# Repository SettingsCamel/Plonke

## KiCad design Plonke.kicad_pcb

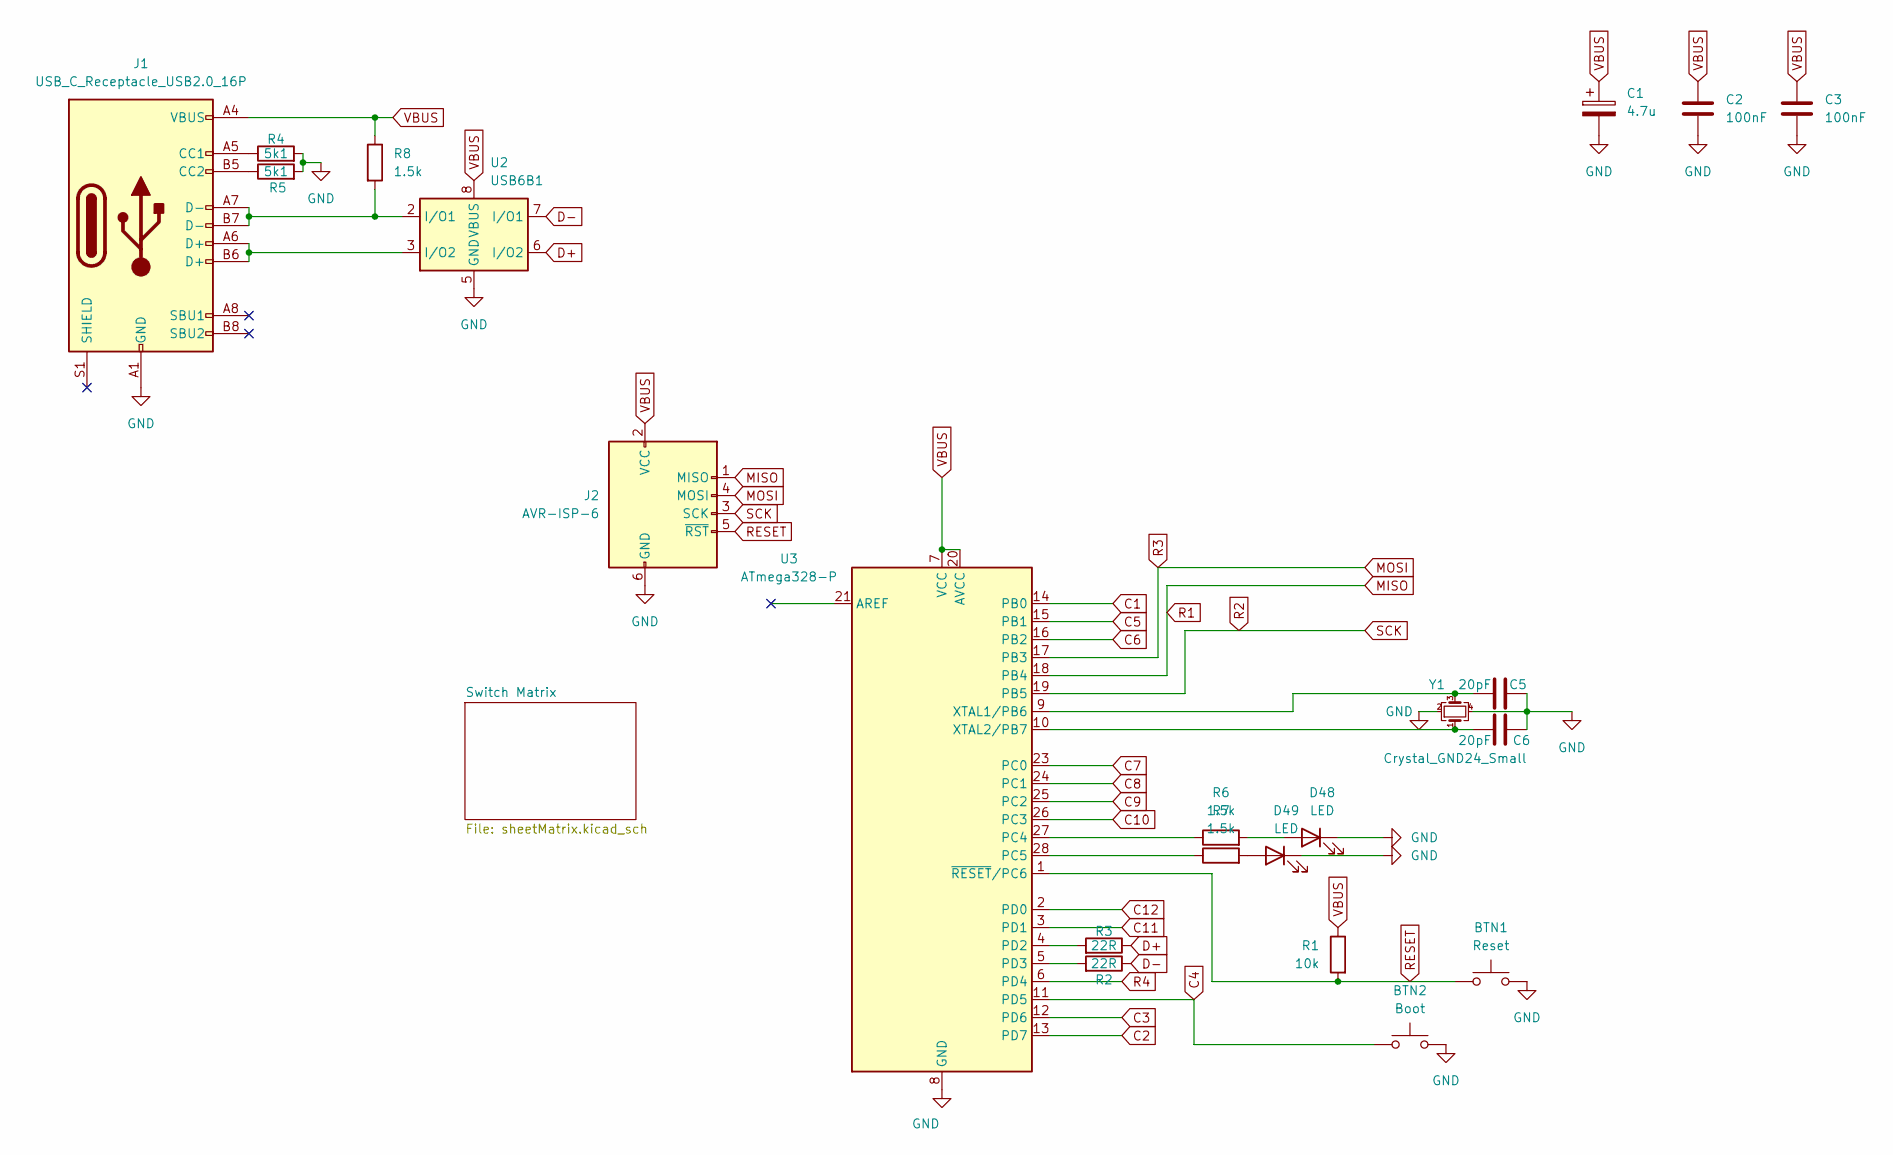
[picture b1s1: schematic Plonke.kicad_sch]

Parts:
BTN1: Reset; SW_PUSH_6mm
BTN2: Boot; SW_PUSH_6mm
C1: 4.7u; CP_Radial_D4.0mm_P1.50mm
C2, C3: 100nF; C_Disc_D4.7mm_W2.5mm_P5.00mm
C5, C6: 20pF; C_Disc_D4.7mm_W2.5mm_P5.00mm
D48, D49: LED; LED_D3.0mm
J1: USB_C_Receptacle_USB2.0_16P; USB_C_Receptacle_XKB_U262-16XN-4BVC11
J2: AVR-ISP-6; PinHeader_2x03_P2.54mm_Vertical
R1: 10k; R_Axial_DIN0207_L6.3mm_D2.5mm_P10.16mm_Horizontal
R2, R3: 22R; R_Axial_DIN0207_L6.3mm_D2.5mm_P10.16mm_Horizontal
R4, R5: 5k1; R_Axial_DIN0207_L6.3mm_D2.5mm_P10.16mm_Horizontal
R6, R7, R8: 1.5k; R_Axial_DIN0207_L6.3mm_D2.5mm_P10.16mm_Horizontal
U2: USB6B1; SOIC-8_3.9x4.9mm_P1.27mm
U3: ATmega328-P; DIP-28_W7.62mm
Y1: Crystal_GND24_Small; Crystal_HC18-U_Vertical

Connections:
C1: U3.14 (PB0); also elsewhere on the board
C2: U3.13 (PD7); also elsewhere on the board
C3: U3.12 (PD6); also elsewhere on the board
C4: BTN2.2, U3.11 (PD5); also elsewhere on the board
C5: U3.15 (PB1); also elsewhere on the board
C6: U3.16 (PB2); also elsewhere on the board
C7: U3.23 (PC0); also elsewhere on the board
C8: U3.24 (PC1); also elsewhere on the board
C9: U3.25 (PC2); also elsewhere on the board
C10: U3.26 (PC3); also elsewhere on the board
C11: U3.3 (PD1); also elsewhere on the board
C12: U3.2 (PD0); also elsewhere on the board
D+: R3.1, U2.6 (I/O2)
D-: R2.1, U2.7 (I/O1)
GND: BTN1.1, BTN2.1, C1.2, C2.2, C3.2, C5.1, C6.1, D48.1 (K), D49.1 (K), J1.A1 (GND), J1.A12 (GND), J1.B1 (GND), J1.B12 (GND), J2.6 (GND), R4.2, R5.2, U2.4 (GND), U2.5 (GND), U3.8 (GND), U3.22 (GND), Y1.2, Y1.4
MISO: J2.1 (MISO), U3.18 (PB4); also elsewhere on the board
MOSI: J2.4 (MOSI), U3.17 (PB3); also elsewhere on the board
unnamed: D48.2 (A), R6.2
unnamed: D49.2 (A), R7.2
unnamed: J1.A5 (CC1), R4.1
unnamed: J1.B5 (CC2), R5.1
unnamed: J1.A6 (D+), J1.B6 (D+), U2.3 (I/O2)
unnamed: J1.A7 (D-), J1.B7 (D-), R8.2, U2.2 (I/O1)
unnamed: R6.1, U3.27 (PC4)
unnamed: R7.1, U3.28 (PC5)
unnamed: R3.2, U3.4 (PD2)
unnamed: R2.2, U3.5 (PD3)
unnamed: C5.2, U3.9 (XTAL1/PB6), Y1.3
unnamed: C6.2, U3.10 (XTAL2/PB7), Y1.1
R2: J2.3 (SCK), U3.19 (PB5); also elsewhere on the board
R4: U3.6 (PD4); also elsewhere on the board
RESET: BTN1.2, J2.5 (~RST), R1.2, U3.1 (~RESET/PC6)
VBUS: C1.1, C2.1, C3.1, J1.A4 (VBUS), J1.A9 (VBUS), J1.B4 (VBUS), J1.B9 (VBUS), J2.2 (VCC), R1.1, R8.1, U2.1 (VBUS), U2.8 (VBUS), U3.7 (VCC), U3.20 (AVCC)

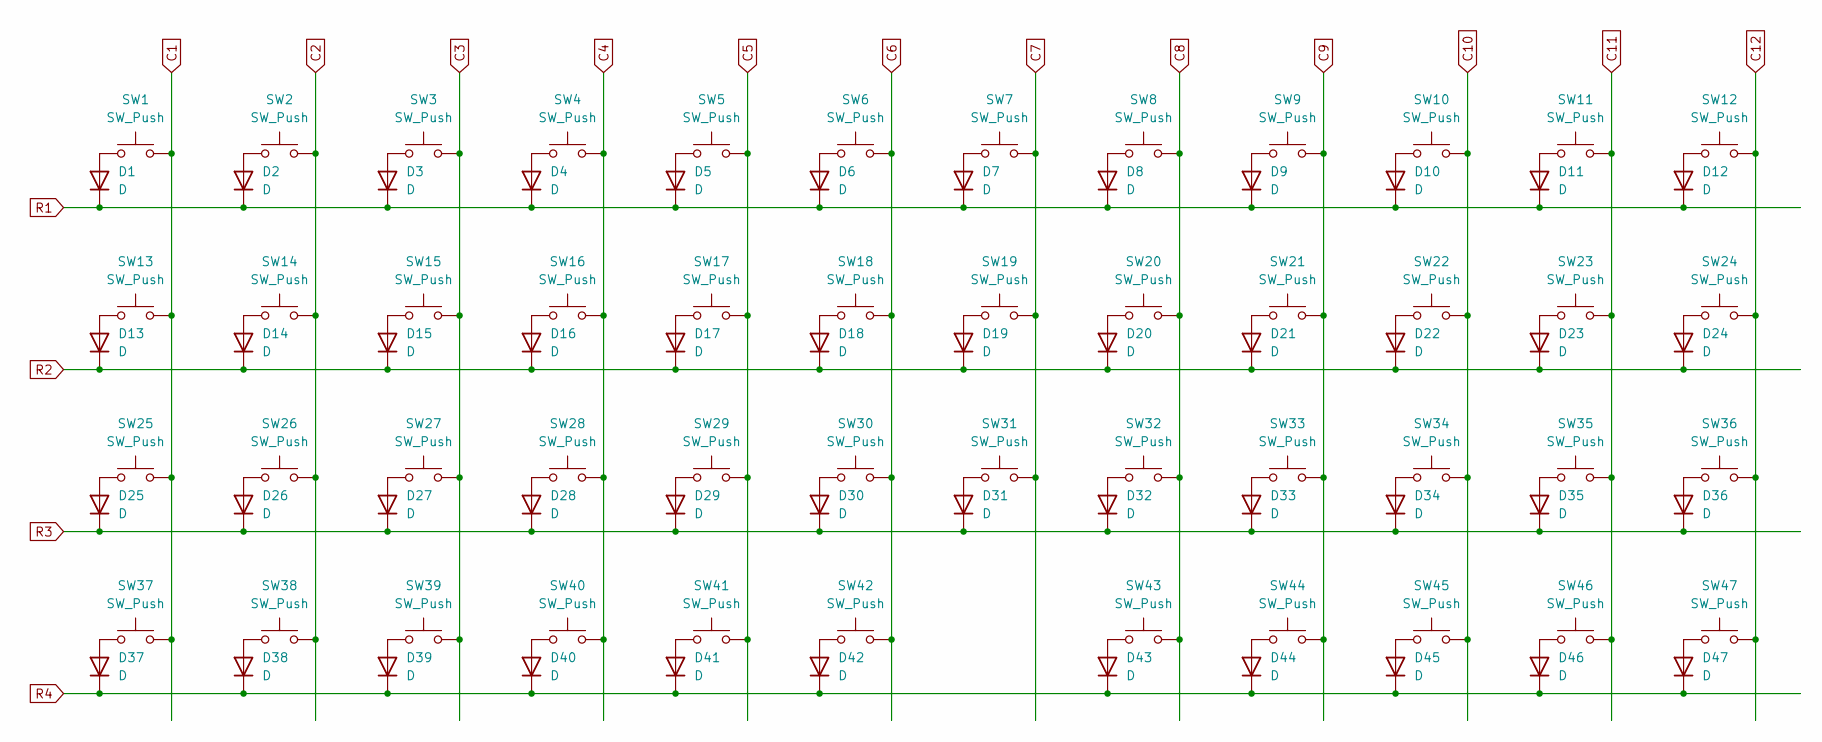
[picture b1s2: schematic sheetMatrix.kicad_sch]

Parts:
D1, D2, D3, D4, D5, D6, D7, D8, D9, D10, D11, D12, D13, D14, D15, D16, D17, D18, D19, D20, D21, D22, D23, D24, D25, D26, D27, D28, D29, D30, D31, D32, D33, D34, D35, D36, D37, D38, D39, D40, D41, D42, D43, D44, D45, D46, D47: D; D_A-405_P7.62mm_Horizontal
SW1, SW2, SW3, SW4, SW5, SW6, SW7, SW8, SW9, SW10, SW11, SW12, SW13, SW14, SW15, SW16, SW17, SW18, SW19, SW20, SW21, SW22, SW23, SW24, SW25, SW26, SW27, SW28, SW29, SW30, SW31, SW32, SW33, SW34, SW35, SW36, SW37, SW38, SW39, SW40, SW41, SW43, SW44, SW45, SW46, SW47: SW_Push; MX-Hotswap-1U
SW42: SW_Push; MX-Hotswap-2U

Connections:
C1: SW1.2, SW13.2, SW25.2, SW37.2; also elsewhere on the board
C2: SW2.2, SW14.2, SW26.2, SW38.2; also elsewhere on the board
C3: SW3.2, SW15.2, SW27.2, SW39.2; also elsewhere on the board
C4: SW4.2, SW16.2, SW28.2, SW40.2; also elsewhere on the board
C5: SW5.2, SW17.2, SW29.2, SW41.2; also elsewhere on the board
C6: SW6.2, SW18.2, SW30.2, SW42.2; also elsewhere on the board
C7: SW7.2, SW19.2, SW31.2; also elsewhere on the board
C8: SW8.2, SW20.2, SW32.2, SW43.2; also elsewhere on the board
C9: SW9.2, SW21.2, SW33.2, SW44.2; also elsewhere on the board
C10: SW10.2, SW22.2, SW34.2, SW45.2; also elsewhere on the board
C11: SW11.2, SW23.2, SW35.2, SW46.2; also elsewhere on the board
C12: SW12.2, SW24.2, SW36.2, SW47.2; also elsewhere on the board
MISO: D1.1 (K), D2.1 (K), D3.1 (K), D4.1 (K), D5.1 (K), D6.1 (K), D7.1 (K), D8.1 (K), D9.1 (K), D10.1 (K), D11.1 (K), D12.1 (K); also elsewhere on the board
MOSI: D25.1 (K), D26.1 (K), D27.1 (K), D28.1 (K), D29.1 (K), D30.1 (K), D31.1 (K), D32.1 (K), D33.1 (K), D34.1 (K), D35.1 (K), D36.1 (K); also elsewhere on the board
unnamed: D1.2 (A), SW1.1
unnamed: D2.2 (A), SW2.1
unnamed: D3.2 (A), SW3.1
unnamed: D4.2 (A), SW4.1
unnamed: D5.2 (A), SW5.1
unnamed: D6.2 (A), SW6.1
unnamed: D7.2 (A), SW7.1
unnamed: D8.2 (A), SW8.1
unnamed: D9.2 (A), SW9.1
unnamed: D10.2 (A), SW10.1
unnamed: D11.2 (A), SW11.1
unnamed: D12.2 (A), SW12.1
unnamed: D13.2 (A), SW13.1
unnamed: D14.2 (A), SW14.1
unnamed: D15.2 (A), SW15.1
unnamed: D16.2 (A), SW16.1
unnamed: D17.2 (A), SW17.1
unnamed: D18.2 (A), SW18.1
unnamed: D19.2 (A), SW19.1
unnamed: D20.2 (A), SW20.1
unnamed: D21.2 (A), SW21.1
unnamed: D22.2 (A), SW22.1
unnamed: D23.2 (A), SW23.1
unnamed: D24.2 (A), SW24.1
unnamed: D25.2 (A), SW25.1
unnamed: D26.2 (A), SW26.1
unnamed: D27.2 (A), SW27.1
unnamed: D28.2 (A), SW28.1
unnamed: D29.2 (A), SW29.1
unnamed: D30.2 (A), SW30.1
unnamed: D31.2 (A), SW31.1
unnamed: D32.2 (A), SW32.1
unnamed: D33.2 (A), SW33.1
unnamed: D34.2 (A), SW34.1
unnamed: D35.2 (A), SW35.1
unnamed: D36.2 (A), SW36.1
unnamed: D37.2 (A), SW37.1
unnamed: D38.2 (A), SW38.1
unnamed: D39.2 (A), SW39.1
unnamed: D40.2 (A), SW40.1
unnamed: D41.2 (A), SW41.1
unnamed: D42.2 (A), SW42.1
unnamed: D43.2 (A), SW43.1
unnamed: D44.2 (A), SW44.1
unnamed: D45.2 (A), SW45.1
unnamed: D46.2 (A), SW46.1
unnamed: D47.2 (A), SW47.1
R2: D13.1 (K), D14.1 (K), D15.1 (K), D16.1 (K), D17.1 (K), D18.1 (K), D19.1 (K), D20.1 (K), D21.1 (K), D22.1 (K), D23.1 (K), D24.1 (K); also elsewhere on the board
R4: D37.1 (K), D38.1 (K), D39.1 (K), D40.1 (K), D41.1 (K), D42.1 (K), D43.1 (K), D44.1 (K), D45.1 (K), D46.1 (K), D47.1 (K); also elsewhere on the board

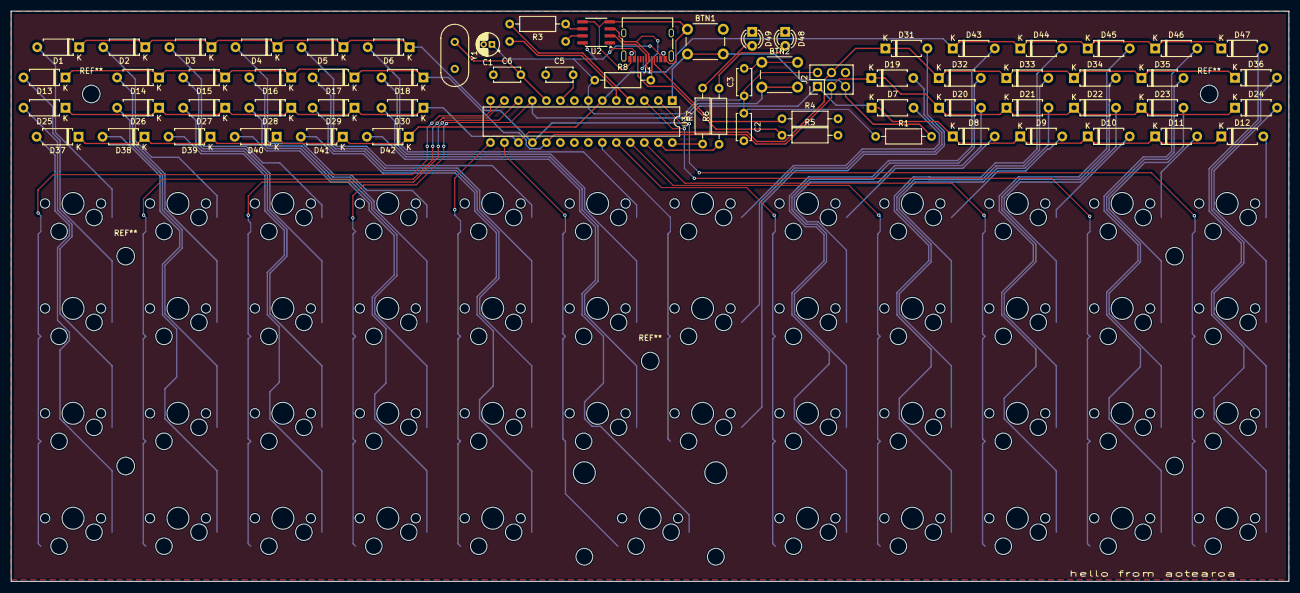
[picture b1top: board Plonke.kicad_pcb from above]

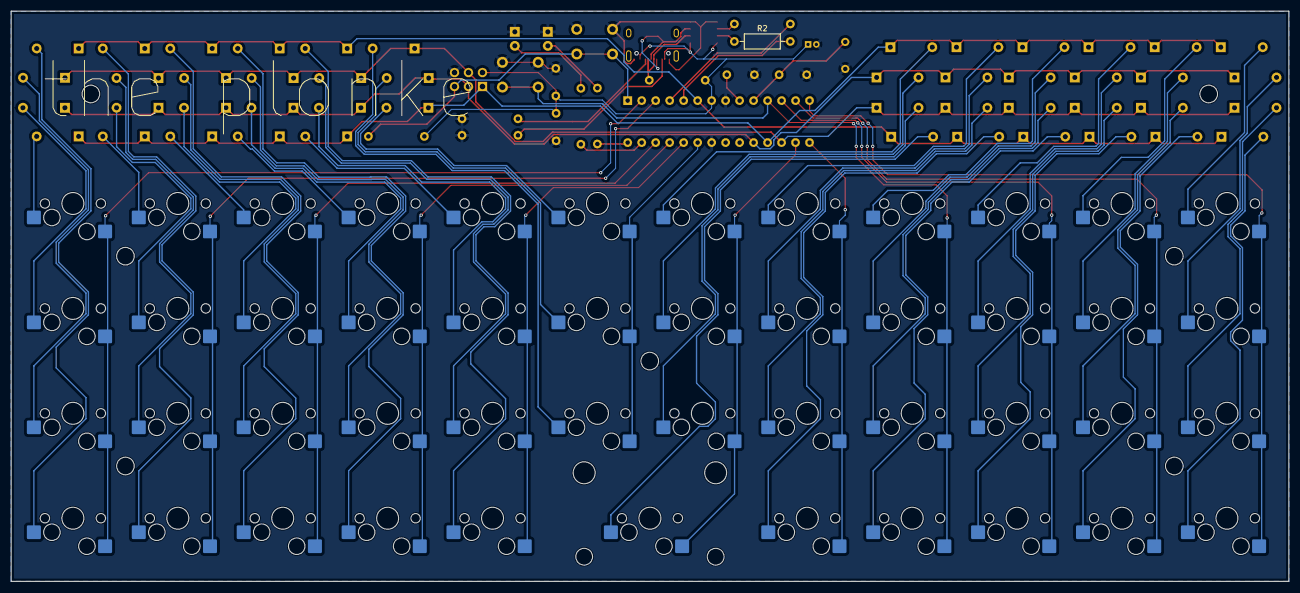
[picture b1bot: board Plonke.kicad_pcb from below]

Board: 2 copper layers, 232.0 x 103.5 mm, 116 parts (48 on the bottom side), 80 nets.

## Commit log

2025-12-31 tim plz help me
    many many changes
2026-01-16 i did this
2026-01-17 Delete Plonke-backups directory
    clean this up a little
2026-01-17 Routing "done"
    needs drc now.
    sent from my iphone
